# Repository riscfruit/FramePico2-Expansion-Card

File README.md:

# FramePico2-Expansion-Card
A USB Type-C devboard dongle based on RP2354, with 2 ports, in expansion card form factor. Soon available on Crowd Supply.

### Gallery

### License
Copyright (c) 2026, Riscfruit Laboratory. This open source hardware is released under [CERN-OHL-S-2.0](LICENSE).

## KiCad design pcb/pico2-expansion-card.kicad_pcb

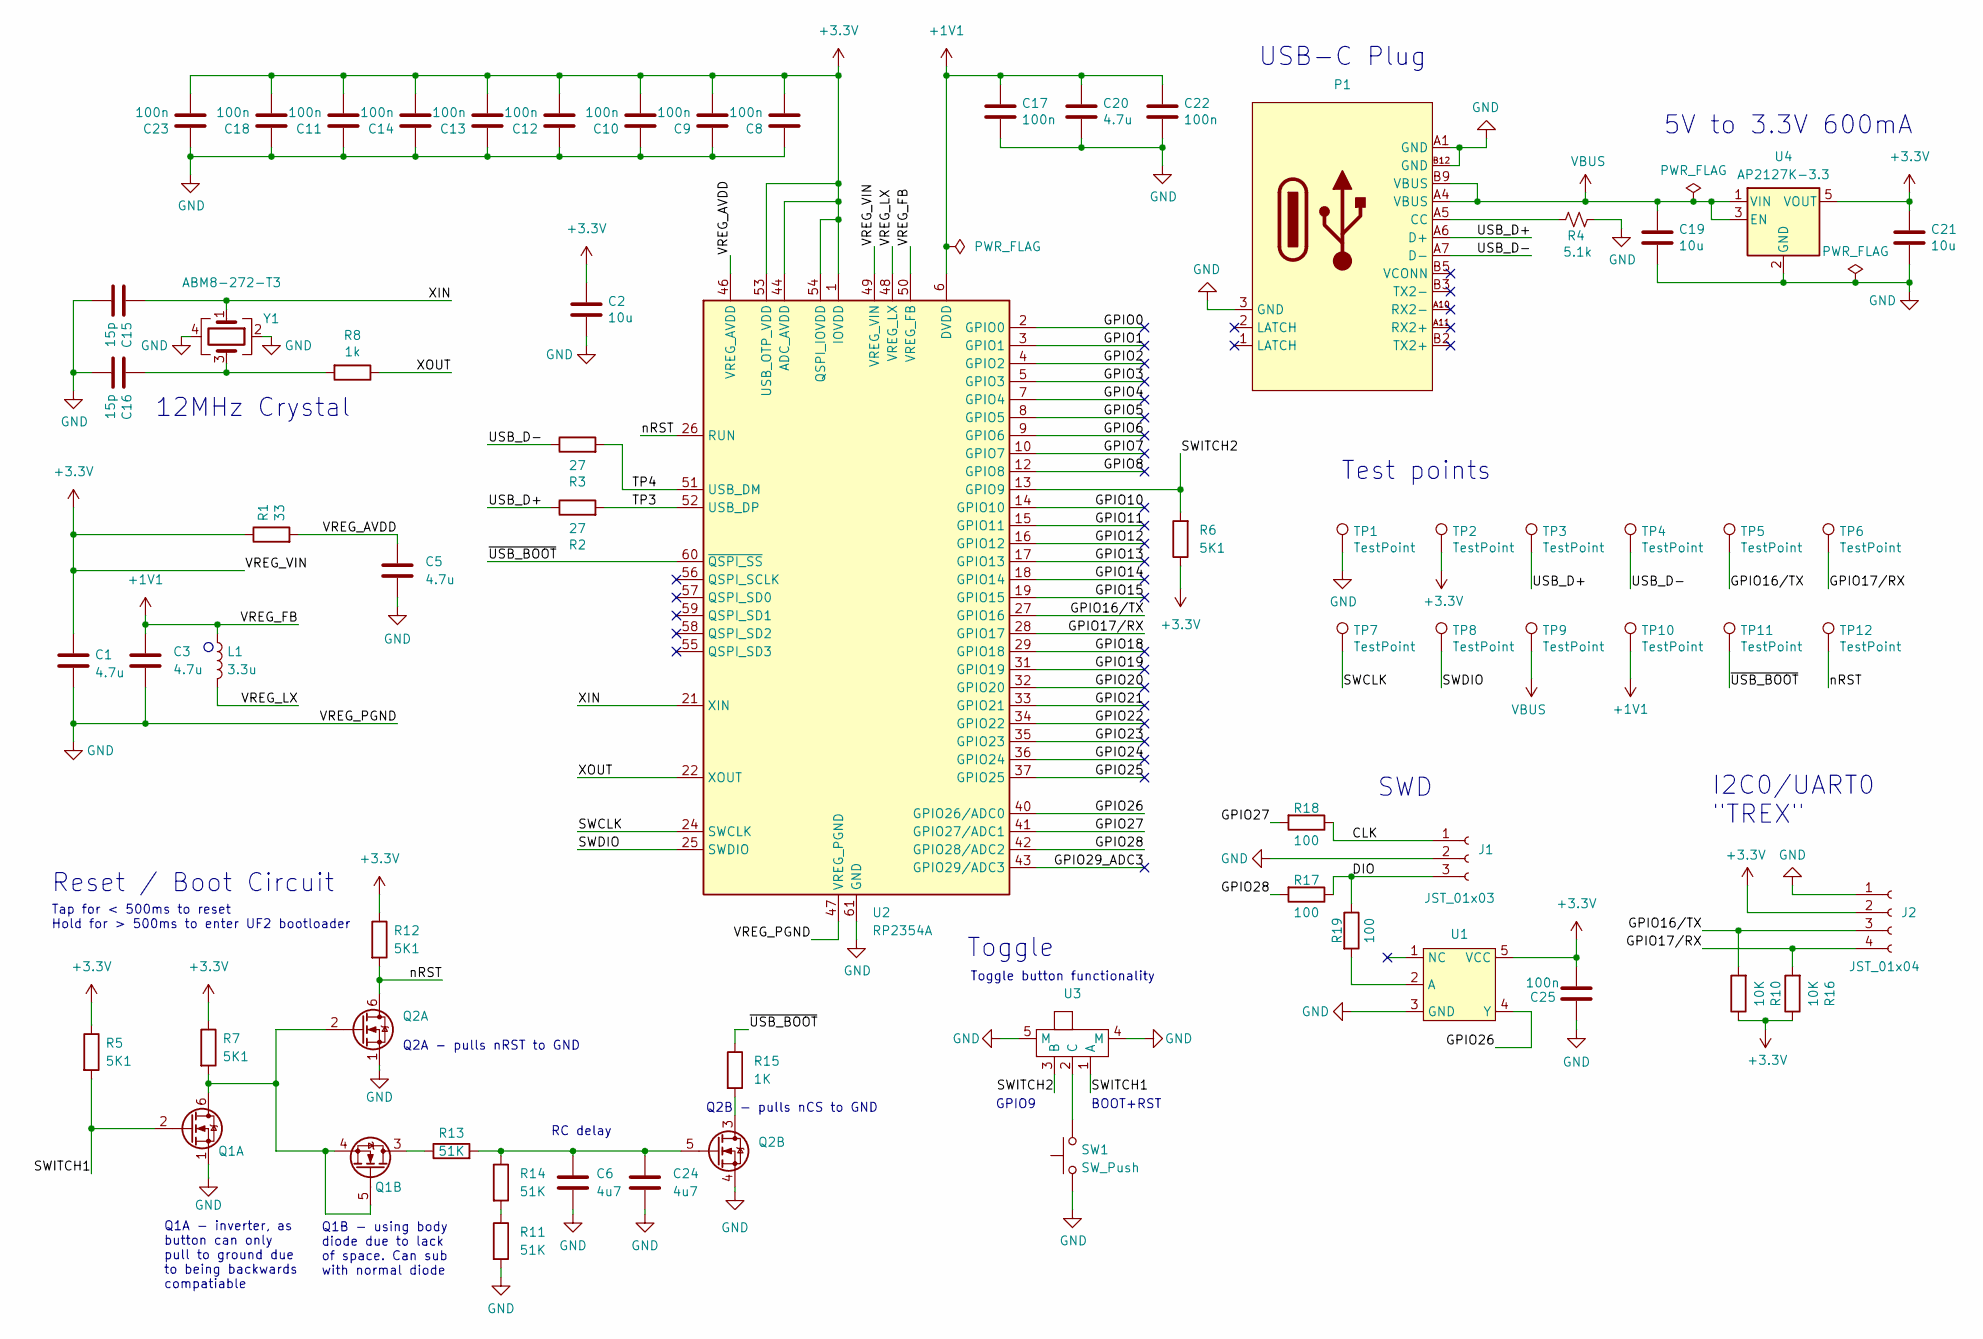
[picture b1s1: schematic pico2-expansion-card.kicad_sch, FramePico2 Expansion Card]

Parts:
C1, C3: 4.7u; C_0402_1005Metric_small_pads
C2, C19, C21: 10u; C_0805_2012Metric
C5, C20: 4.7u; C_0402_1005Metric
C6, C24: 4u7; C_0402_1005Metric; MPN CL05A475MP5NRNC; JLC Basic Y
C8, C9, C10, C11, C12, C13, C14, C17, C18, C22, C23, C25: 100n; C_0402_1005Metric
C15, C16: 15p; C_0402_1005Metric
J1: JST_01x03; JST_SH_SM03B-SRSS-TB_1x03-1MP_P1.00mm_Horizontal
J2: JST_01x04; JST_SH_SM04B-SRSS-TB_1x04-1MP_P1.00mm_Horizontal
L1: 3.3u; IND-SMD_L2.0-W1.6_AOTA-B201610S3R3-101-T
P1: USB-C-SMD_TYPE-C-31-G-10
Q1, Q2: EM6K6; SOT-563; MPN 2N7002V; JLC Basic N
R1: 33; R_0402_1005Metric
R2, R3: 27; R_0402_1005Metric
R4: 5.1k; R_0402_1005Metric
R5, R6, R7, R12: 5K1; R_0402_1005Metric; MPN 0402WGF5101TCE; LCSC C25905
R8: 1k; R_0402_1005Metric
R10, R16: 10K; R_0402_1005Metric
R11, R13, R14: 51K; R_0402_1005Metric; MPN 0402WGF5102TCE; JLC Basic Y
R15: 1K; R_0402_1005Metric; MPN 0402WGF1001TCE; LCSC C11702
R17, R18, R19: 100; R_0402_1005Metric
SW1: SW_Push; BUTTON-SW-SMD_2P-TS24CA
TP1, TP2, TP3, TP4, TP5, TP6, TP7, TP8, TP9, TP10, TP11, TP12: TestPoint; TestPoint_Pad_1.0x1.0mm
U1: TECH PUBLIC TP74AUP1T17C5
U2: RP2354A; RP2350-QFN-60-1EP_7x7_P0.4mm_EP3.4x3.4mm_ThermalVias
U3: SW-SMD_SSAJ120100
U4: AP2127K-3.3; SOT-23-5
Y1: ABM8-272-T3; Crystal_SMD_3225-4Pin_3.2x2.5mm

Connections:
+1V1: C3.1, C17.1, C20.1, C22.1, L1.1, TP10.1 (1_1), U2.6 (DVDD), U2.23 (DVDD), U2.39 (DVDD), U2.50 (VREG_FB)
+3.3V: C1.1, C2.1, C8.2, C9.2, C10.2, C11.2, C12.2, C13.2, C14.2, C18.2, C21.1, C23.2, C25.2, J2.2, R1.1, R5.1, R6.1, R7.1, R10.1, R12.1, R16.1, TP2.1 (1_1), U1.5 (VCC), U2.1 (IOVDD), U2.11 (IOVDD), U2.20 (IOVDD), U2.30 (IOVDD), U2.38 (IOVDD), U2.44 (ADC_AVDD), U2.45 (IOVDD), U2.49 (VREG_VIN), U2.53 (USB_OTP_VDD), U2.54 (QSPI_IOVDD), U4.5 (VOUT)
/CLK: J1.1, R18.1
/DIO: J1.3, R17.1, R19.1
/GPIO0: U2.2 (GPIO0)
/GPIO1: U2.3 (GPIO1)
/GPIO2: U2.4 (GPIO2)
/GPIO3: U2.5 (GPIO3)
/GPIO4: U2.7 (GPIO4)
/GPIO5: U2.8 (GPIO5)
/GPIO6: U2.9 (GPIO6)
/GPIO7: U2.10 (GPIO7)
/GPIO8: U2.12 (GPIO8)
/GPIO10: U2.14 (GPIO10)
/GPIO11: U2.15 (GPIO11)
/GPIO12: U2.16 (GPIO12)
/GPIO13: U2.17 (GPIO13)
/GPIO14: U2.18 (GPIO14)
/GPIO15: U2.19 (GPIO15)
/GPIO16/TX: J2.3, R10.2, TP5.1 (1_1), U2.27 (GPIO16)
/GPIO17/RX: J2.4, R16.2, TP6.1 (1_1), U2.28 (GPIO17)
/GPIO18: U2.29 (GPIO18)
/GPIO19: U2.31 (GPIO19)
/GPIO20: U2.32 (GPIO20)
/GPIO21: U2.33 (GPIO21)
/GPIO22: U2.34 (GPIO22)
/GPIO23: U2.35 (GPIO23)
/GPIO24: U2.36 (GPIO24)
/GPIO25: U2.37 (GPIO25)
/GPIO26: U1.4 (Y), U2.40 (GPIO26/ADC0)
/GPIO27: R18.2, U2.41 (GPIO27/ADC1)
/GPIO28: R17.2, U2.42 (GPIO28/ADC2)
/GPIO29_ADC3: U2.43 (GPIO29/ADC3)
/SWCLK: TP7.1 (1_1), U2.24 (SWCLK)
/SWDIO: TP8.1 (1_1), U2.25 (SWDIO)
/SWITCH1: Q1.2 (G), R5.2, U3.1 (A)
/TP3: R2.2, U2.52 (USB_DP)
/TP4: R3.2, U2.51 (USB_DM)
/USB_D+: P1.A6 (D+), R2.1, TP3.1 (1_1)
/USB_D-: P1.A7 (D-), R3.1, TP4.1 (1_1)
/VREG_AVDD: C5.1, R1.2, U2.46 (VREG_AVDD)
/VREG_LX: L1.2, U2.48 (VREG_LX)
/XIN: C15.1, U2.21 (XIN), Y1.1
/XOUT: R8.1, U2.22 (XOUT)
/nRST: Q2.6 (D), R12.2, TP12.1 (1_1), U2.26 (RUN)
/~USB_BOOT: R15.1, TP11.1 (1_1), U2.60 (~QSPI_SS)
GND: C1.2, C2.2, C3.2, C5.2, C6.2, C8.1, C9.1, C10.1, C11.1, C12.1, C13.1, C14.1, C15.2, C16.2, C17.2, C18.1, C19.2, C20.2, C21.2, C22.2, C23.1, C24.2, C25.1, J1.2, J2.1, P1.3 (GND), P1.A1 (GND), P1.B12 (GND), Q1.1 (S), Q2.1 (S), Q2.4 (S), R4.2, R11.2, SW1.1, TP1.1 (1_1), U1.3 (GND), U2.47 (VREG_PGND), U2.61 (GND), U3.4 (M), U3.5 (M), U4.2 (GND), Y1.2, Y1.4
unnamed: C16.1, R8.2, Y1.3
unnamed: P1.A5 (CC), R4.1
unnamed: Q1.4 (S), Q1.5 (G), Q1.6 (D), Q2.2 (G), R7.2
unnamed: Q1.3 (D), R13.1
unnamed: Q2.3 (D), R15.2
unnamed: C6.1, C24.1, Q2.5 (G), R13.2, R14.1
unnamed: R11.1, R14.2
unnamed: R19.2, U1.2 (A)
VBUS: C19.1, P1.A4 (VBUS), P1.B9 (VBUS), TP9.1 (1_1), U4.1 (VIN), U4.3 (EN)

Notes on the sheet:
Q2B - pulls nCS to GND
Tap for < 500ms to reset Hold for > 500ms to enter UF2 bootloader
USB-C Plug
Q1B - using body diode due to lack of space. Can sub with normal diode
12MHz Crystal
BOOT+RST
Reset / Boot Circuit
Q1A - inverter, as button can only pull to ground due to being backwards compatiable
5V to 3.3V 600mA
I2C0/UART0 "TREX"
Toggle
GPIO9
Test points
SWD
RC delay
Q2A - pulls nRST to GND
Toggle button functionality

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
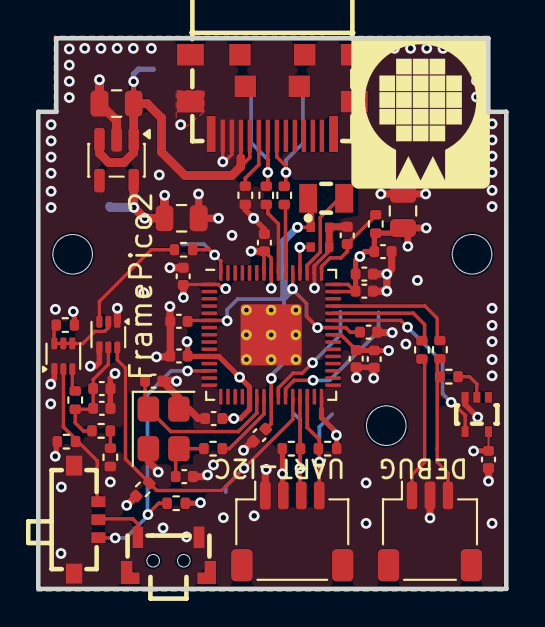
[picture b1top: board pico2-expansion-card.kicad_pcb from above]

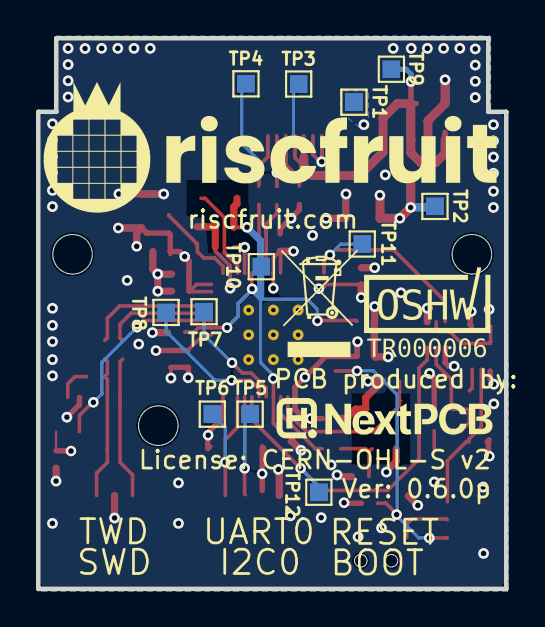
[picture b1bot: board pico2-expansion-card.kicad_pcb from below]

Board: 4 copper layers, 26.0 x 30.6 mm, 68 parts (12 on the bottom side), 34 nets.

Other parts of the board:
H1, H1#2, H1#3: MountingHole; MountingHole_2.2mm_M2

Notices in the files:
pcb/pico2-expansion-card.kicad_pcb:
License: CERN-OHL-S
License: CERN-OHL-S v2
